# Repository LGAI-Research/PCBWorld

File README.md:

# PCBWorld

PCBWorld <!--VERSION-->v1.2.2<!--/VERSION-->,
from LG AI Research: an open-source Gymnasium environment for PCB routing, built on KiCad's
interactive router.

It runs on Linux x86_64 (primary) and on macOS with Apple Silicon (experimental,
[see below](#macos-apple-silicon)). The environment is BSD-3-Clause; the engine is GPLv3
(see [Licensing](#licensing)). The engine submodule pins KiCad 9.0.8.

PCBWorld wraps KiCad's push-and-shove router as a [Gymnasium](https://gymnasium.farama.org/)
environment. An agent places tracks and vias on a real `.kicad_pcb` board, and every step is
scored by KiCad's own design-rule checker. What routes here routes in KiCad.

The repository ships the environment, synthetic board generators, the real-board benchmark
splits, one evaluation pipeline shared by every method, and three families of baselines:
a decoder-only PPO/GRPO transformer, LLM tool-calling agents, and the rule-based routers
Freerouting and KRT.

## Demo

An LLM agent routing two production boards end to end (time-lapse; click for the full video):

| `0018_hy_adapter` | `0100_smt-zvs-driver` |
|---|---|
|  |  |

All supplementary videos: [PCBWorld_media/index.html](PCBWorld_media/index.html).

## Using the environment

```python
from configs.loader.schema import EnvConfig
from pcb_world.core.env import PCBWorld
from pcb_world.core.action_schema import ACT_NET_SELECT, ACT_START_ROUTE, ACT_MAKE_LINE, ACT_NET_END

# EnvConfig: every env setting (defaults: configs/env.yaml)
env = PCBWorld("tests/fixtures/simple_routing_board.kicad_pcb", EnvConfig.with_overrides(max_steps=200))
obs, info = env.reset(seed=0)

src, dst = obs["board_static"]["nets"]["net_1"]["pads"].values()
(x0, y0), (x1, y1) = src["center"]["xy"], dst["center"]["xy"]

for action in (
    {"action_type": ACT_NET_SELECT, "net_id": 1},
    {"action_type": ACT_START_ROUTE, "x_mm": x0, "y_mm": y0, "layer": src["layer"]},
    {"action_type": ACT_MAKE_LINE, "x_mm": x1, "y_mm": y1, "routing_mode": 2},
    {"action_type": ACT_NET_END},
):
    obs, reward, terminated, truncated, info = env.step(action)
```

State, actions and reward: [docs/ENVIRONMENT.md](docs/ENVIRONMENT.md).

## Quick start

### 1. Setup

```bash
git clone --recursive https://github.com/LGAI-Research/PCBWorld.git pcbworld && cd pcbworld
bash tools/setup/setup_all.sh        # conda env, pinned baselines, engine build, import smoke
conda activate pcbworld && export PYTHONPATH=build_rl/pcbnew/python/rl:. PCBWORLD_DATA_ROOT=$PWD/var/datasets
```

`setup_all.sh` needs conda's libmamba solver (the default from conda 23.10) or `mamba` in conda's base; the
classic solver does not finish on this env, so the script stops and says how to switch
(`SKIP_ENV=1` keeps an existing env without solving).

#### macOS (Apple Silicon)

The same `setup_all.sh` picks [environment.macos.yml](environment.macos.yml) and
[requirements-macos.txt](requirements-macos.txt) on an arm64 Mac; install the Xcode Command Line
Tools first (`xcode-select --install`). The engine is built from the conda env alone; a Homebrew
install is ignored. Rebuild it (after a C++ change) with `bash tools/setup/build_engine.sh`, as on
Linux. This path is experimental. On a Mac:

- **Verified** (Apple M5 Pro, macOS 26.4): `setup_all.sh` end to end (env, baseline downloads, engine
  build, import), the test suite, and the RL quick start (step 3: board generation, PPO training on the
  Apple GPU (MPS), evaluation); KRT's `grid_router` builds with cargo.
- **Not yet verified:** LLM agents through a provider API, full rule-based baseline runs (Freerouting,
  KRT, OrthoRoute), and the optional `pcbnew` / `kicad-cli` builds (`BUILD_PCBNEW=1`, `BUILD_CLI=1`).
- **Linux only:** LLM-policy training (verl-agent) and the local vLLM provider (vLLM ships no macOS
  build), the CUDA kernels (flash-attn), and multi-GPU training (NCCL).
- **Unsupported:** Intel Macs (no PyTorch 2.8 build for x86_64 macOS).

### 2. Open-source boards (D3)

```bash
bash tools/quickstart/prepare_pcbench.sh --limit 30 --workers 8
```

Collects the [PCBench](https://github.com/PCBench/PCBench) boards and preprocesses them into the
D3 benchmark set. Drop `--limit` for all of them.

### 3. Train an RL policy

```bash
bash tools/quickstart/train_rl.sh --data-dir var/datasets/synthetic/synth_2L_v2 --boards 200 --iterations 5 --seed 42
```

Generates the boards when the directory is empty, trains PPO on them, and evaluates the policy
on the test split.

### 4. Route with an LLM

```bash
GEMINI_API_KEY=... bash tools/quickstart/run_llm.sh   # or OPENAI_API_KEY, ANTHROPIC_API_KEY, TOGETHER_API_KEY
```

Any one key works; the script picks the provider from it (Gemini has a free tier). Without a key
it only prints the prompt and runs a single fixed step.

The shipped defaults use a newer potential-function combination than the paper. To reproduce the
KDD submission with its original reward, follow [experiments/kdd/](experiments/kdd/README.md).

## Benchmark results

Routing quality on D3-A, the 99 small open-source PCBench boards; the RL policy is trained on
synthetic D2 boards only and routes the D3-A boards zero-shot. Table 3 of the paper (arXiv:2607.05915), under
the @5 protocol of [docs/METRICS.md](docs/METRICS.md); Freerouting and PPO are means over 4 seeds.

| Method | CP ↑ | Pot. ↑ | Rout. ↑ | Time (s) ↓ |
|---|---|---|---|---|
| Reference (the boards' original routed traces) | 1.00 | 23.16 | 1.00 | - |
| Freerouting | 0.80 | **22.71** | 0.91 | 7.09 |
| KRT (KiCadRoutingTools) | 0.74 | 20.00 | 0.94 | 0.65 |
| LLM agent, GPT-5.4 | 0.65 | 19.42 | 0.91 | 231.15 |
| LLM agent, GPT-5.4-mini | 0.28 | 14.22 | 0.72 | 56.85 |
| LLM agent, GPT-5.4-nano | 0.30 | 14.16 | 0.73 | 100.76 |
| LLM agent, Qwen3.5-397B | 0.34 | 14.88 | 0.75 | 81.82 |
| PPO, decoder-only Transformer | **0.86** | 21.46 | 0.95 | 1.83 |

Best CP and Pot. per column of this table, excluding Reference, in bold. The full table (D2, D3-B,
OrthoRoute, the RL variants) is Table 3 of [PCBWorld.pdf](PCBWorld.pdf). Pot. uses the paper's reward, so it is reproduced
through [experiments/kdd/](experiments/kdd/README.md), not the quick start (see above).

The trained policies from the paper are on Hugging Face: [LG-AI-Research/PCBWorld](https://huggingface.co/LG-AI-Research/PCBWorld)
(download notes: [docs/QUICKSTART.md](docs/QUICKSTART.md)).
The checkpoints are licensed separately from this code, under the EXAONE AI Model License Agreement 1.2 - NC:
research and educational use only, with no commercial use of the checkpoints or of their output (see the license in the
Hugging Face repository).

## Licensing

PCBWorld is two programs, distributed separately:

| Program | Where | License |
|---|---|---|
| **PCBWorld**: the environment, agents, benchmark, training and evaluation code | this repository | [BSD-3-Clause](LICENSE) |
| **PCBWorld Engine**: the KiCad modifications, the RL router, the engine server | [LGAI-Research/PCBWorld-Engine](https://github.com/LGAI-Research/PCBWorld-Engine), pinned here as the `engine/` submodule | GPLv3 |

Third-party notices: [Notice.md](Notice.md).

## Citation

Accepted to the KDD 2026 Workshop on Evaluation and Trustworthiness of Agentic AI
([arXiv:2607.05915](https://arxiv.org/abs/2607.05915), [PCBWorld.pdf](PCBWorld.pdf)).

```bibtex
@inproceedings{song2026pcbworld,
  title     = {PCBWorld: A Benchmark Environment for Engine-Grounded
               PCB Design Automation},
  author    = {Song, Hyungseok and Park, Junseok and Choi, Won-Seok and
               Bae, Seohui and Jeong, Han-Seul and Park, Youngjoon and
               Lee, Soonyoung},
  booktitle = {KDD 2026 Workshop on Evaluation and Trustworthiness of
               Agentic AI},
  year      = {2026},
  note      = {arXiv:2607.05915},
}
```

## Contact

Open an issue, or write to yj.park@lgresearch.ai. Bug reports and pull requests are welcome.

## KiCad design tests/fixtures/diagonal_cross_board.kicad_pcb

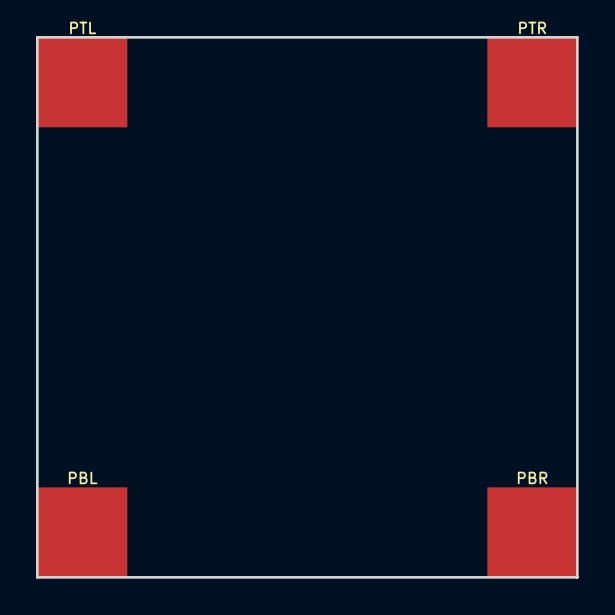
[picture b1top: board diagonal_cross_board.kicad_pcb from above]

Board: 2 copper layers, 30.0 x 30.0 mm, 4 parts (0 on the bottom side), 2 nets, no tracks yet.

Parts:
PBL: N2; FCu
PBR: N1; FCu
PTL: N1; FCu
PTR: N2; FCu

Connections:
NET1: PBR.1, PTL.1
NET2: PBL.1, PTR.1

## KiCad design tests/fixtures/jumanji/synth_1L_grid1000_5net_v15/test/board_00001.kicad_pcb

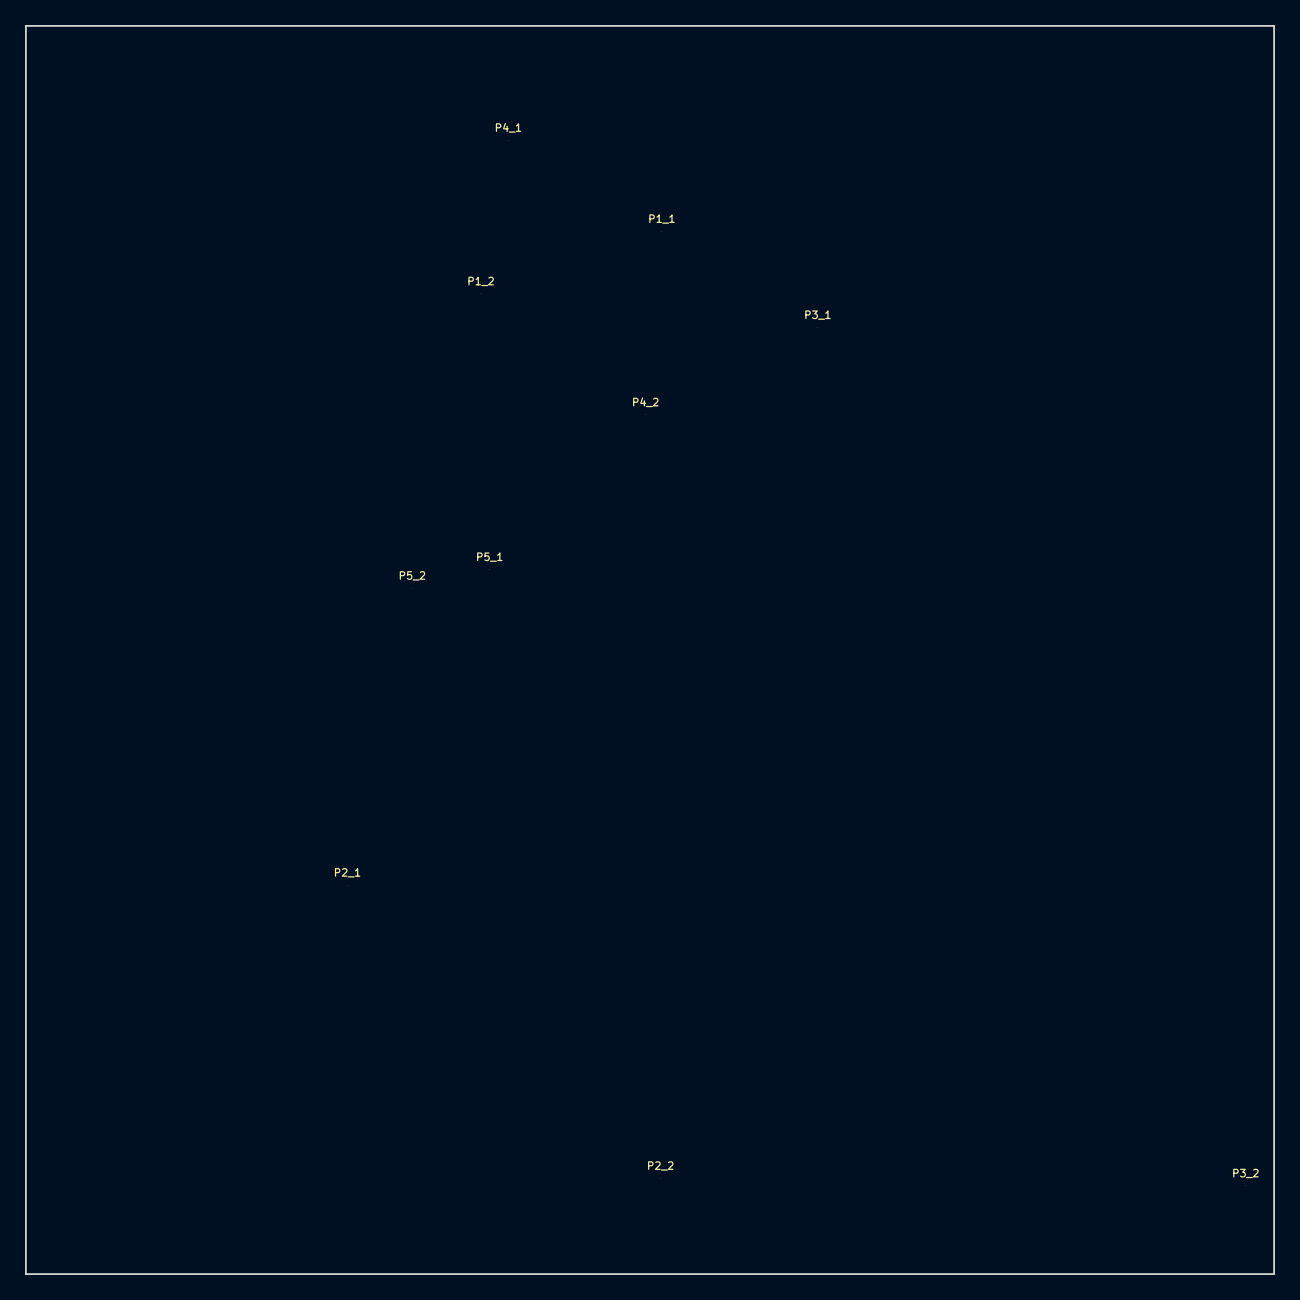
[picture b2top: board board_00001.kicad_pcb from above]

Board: 2 copper layers, 100.0 x 100.0 mm, 10 parts (0 on the bottom side), 5 nets, no tracks yet.

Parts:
P1_1, P2_1, P3_1, P4_1, P5_1: Pad1; FCu
P1_2, P2_2, P3_2, P4_2, P5_2: Pad2; FCu

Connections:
NET1: P1_1.1, P1_2.1
NET2: P2_1.1, P2_2.1
NET3: P3_1.1, P3_2.1
NET4: P4_1.1, P4_2.1
NET5: P5_1.1, P5_2.1

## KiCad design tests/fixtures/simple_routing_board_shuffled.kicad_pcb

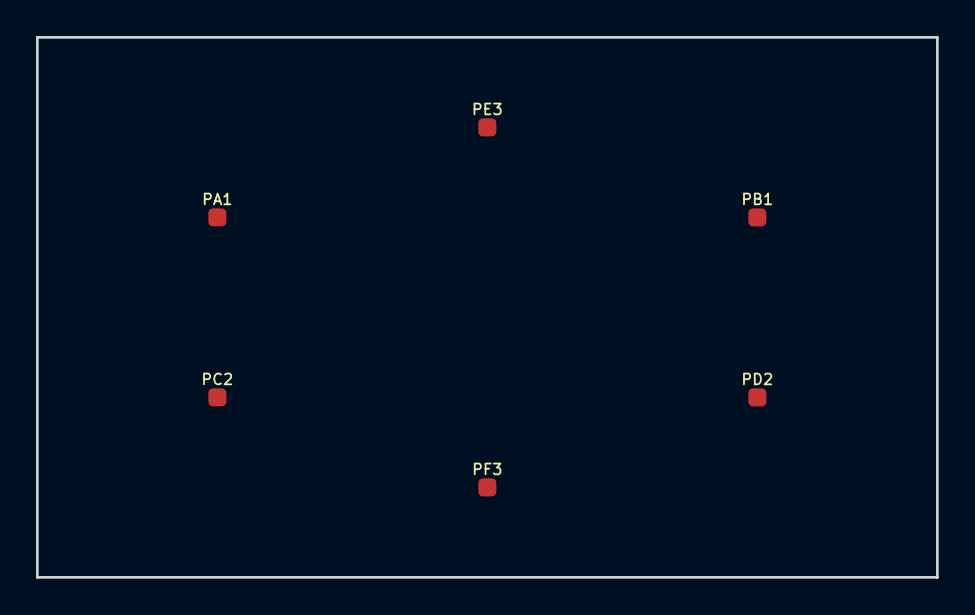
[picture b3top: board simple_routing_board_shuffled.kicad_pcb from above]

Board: 2 copper layers, 50.0 x 30.0 mm, 6 parts (0 on the bottom side), 3 nets, no tracks yet.

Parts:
PA1: Pad1; FCu
PB1: Pad1; FCu
PC2: Pad2; FCu
PD2: Pad2; FCu
PE3: Pad3; FCu
PF3: Pad3; FCu

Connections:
NET1: PE3.1, PF3.1
NET2: PA1.1, PB1.1
NET3: PC2.1, PD2.1

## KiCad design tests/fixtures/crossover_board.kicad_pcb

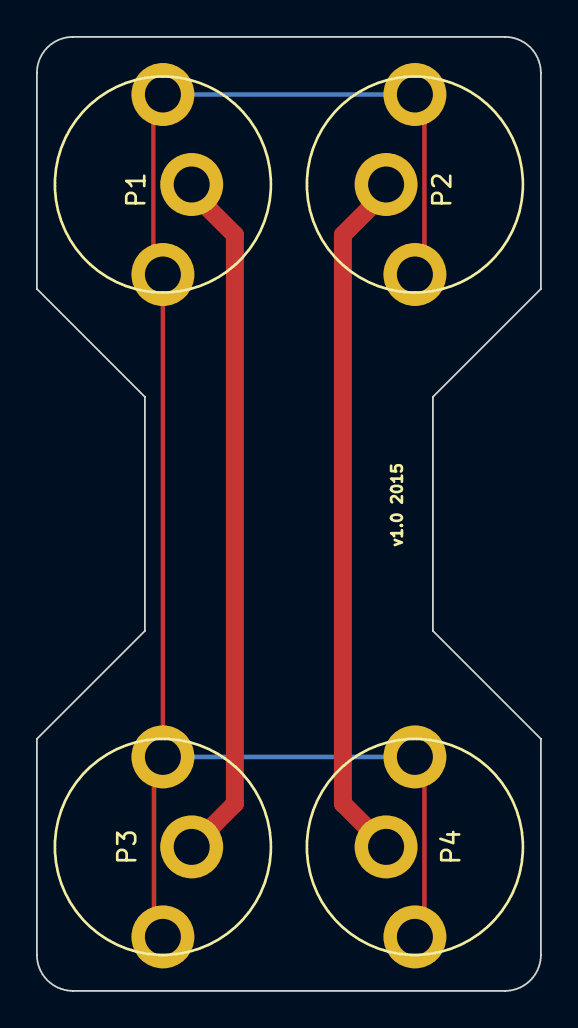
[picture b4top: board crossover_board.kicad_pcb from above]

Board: 2 copper layers, 28.0 x 53.0 mm, 4 parts (0 on the bottom side), 3 nets.

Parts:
P1, P2, P3, P4: bnc_pcb

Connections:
/A: P1.1, P3.1
/B: P2.1, P4.1
GND: P1.2, P2.2, P3.2, P4.2

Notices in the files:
README.md:
License: BSD-3-Clause
